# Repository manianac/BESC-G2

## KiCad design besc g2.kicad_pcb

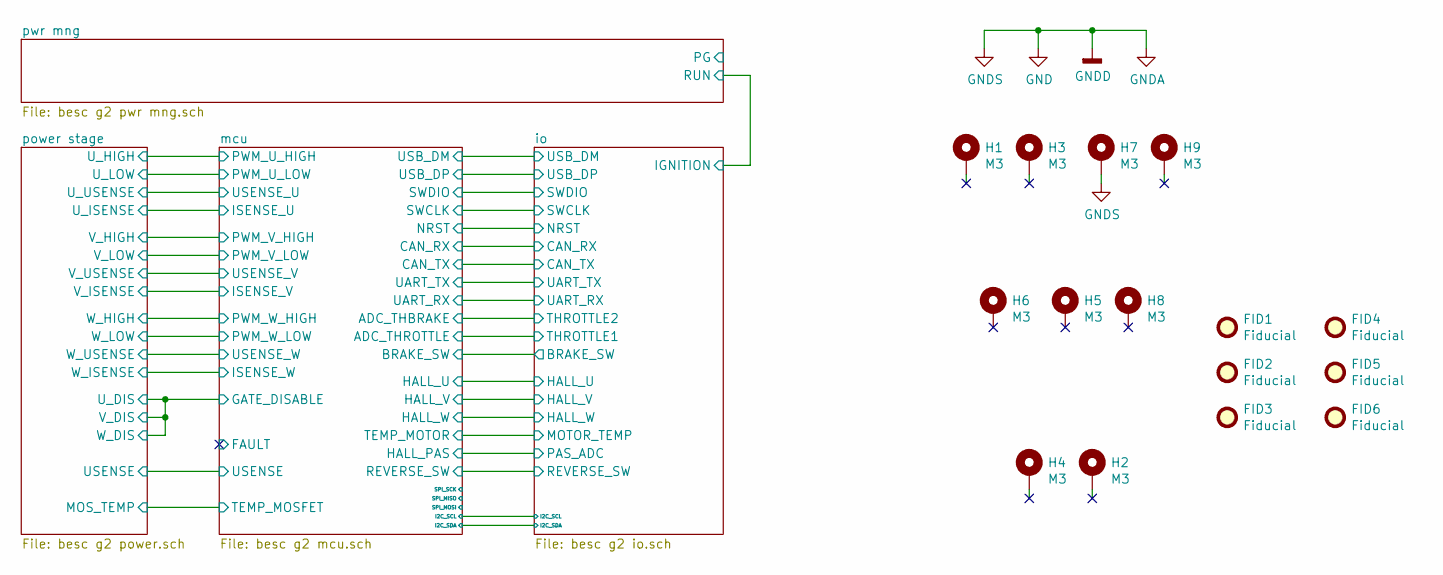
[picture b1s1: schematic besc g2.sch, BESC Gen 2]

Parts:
FID1, FID2, FID3, FID4, FID5, FID6: Fiducial; Fiducial_0.5mm_Mask1.5mm
H1, H2, H3, H4, H5, H6, H7, H8, H9: M3; MountingHole_3.2mm_M3_Pad_Via

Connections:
GND: H7.1; also elsewhere on the board

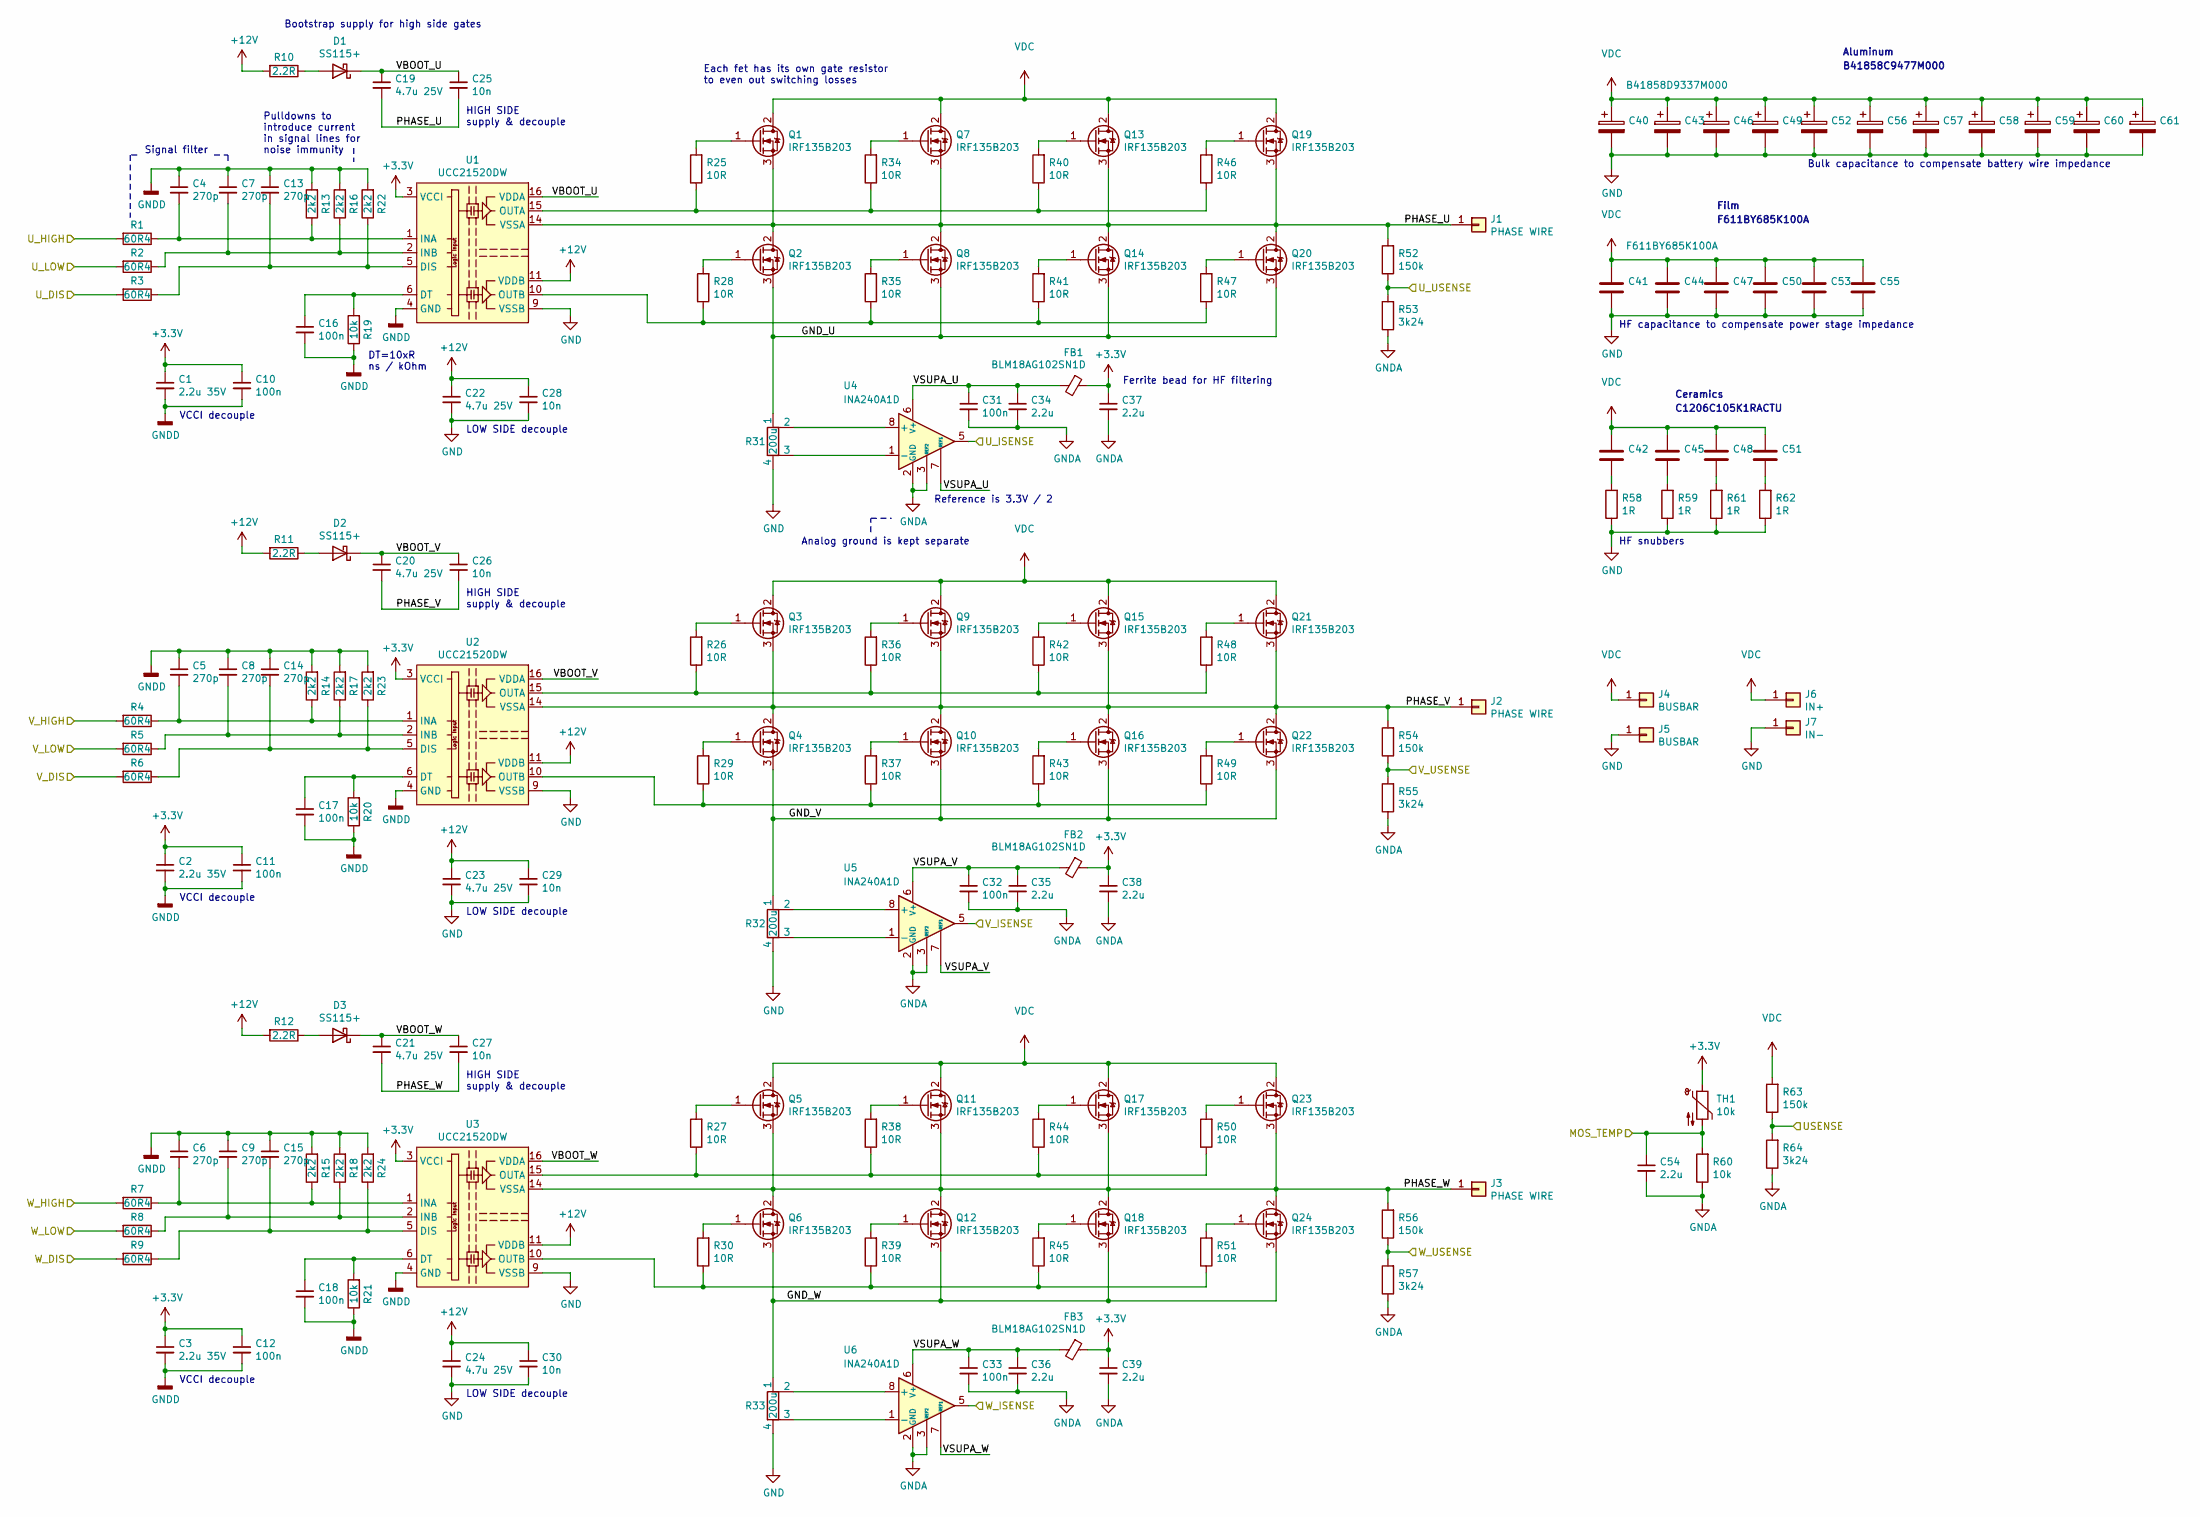
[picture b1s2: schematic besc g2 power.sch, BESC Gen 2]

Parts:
C1, C2, C3: 2.2u 35V; C_0805_2012Metric
C4, C5, C6, C7, C8, C9, C13, C14, C15: 270p; C_0603_1608Metric
C10, C11, C12, C16, C17, C18, C31, C32, C33: 100n; C_0603_1608Metric
C19, C20, C21, C22, C23, C24: 4.7u 25V; C_1206_3216Metric
C25, C26, C27, C28, C29, C30: 10n; C_0603_1608Metric
C34, C35, C36, C37, C38, C39, C54: 2.2u; C_0603_1608Metric
C40, C43, C46, C49, C52, C56, C57, C58, C59, C60, C61: B41858D9337M000; C_Radial_D18.0mm_H25mm_P7.50mm
C41, C44, C47, C50, C53, C55: F611BY685K100A; C_Rect_L18.0mm_W11.0mm_P15.00mm_FKS3_FKP3
C42, C45, C48, C51: C1206C105K1RACTU; C_1206_3216Metric
D1, D2, D3: SS115+; D_SMA
FB1, FB2, FB3: BLM18AG102SN1D; L_0603_1608Metric
J1, J2, J3: PHASE WIRE; 8awg_wirepad
J4, J5: BUSBAR; busbar1
J6: IN+; 8awg_wirepad
J7: IN-; 8awg_wirepad
Q1, Q2, Q3, Q4, Q5, Q6, Q7, Q8, Q9, Q10, Q11, Q12, Q13, Q14, Q15, Q16, Q17, Q18, Q19, Q20, Q21, Q22, Q23, Q24: IRF135B203; TO-220-3_hor_tabup
R1, R2, R3, R4, R5, R6, R7, R8, R9: 60R4; R_0603_1608Metric
R10, R11, R12: 2.2R; R_1206_3216Metric
R13, R14, R15, R16, R17, R18, R22, R23, R24: 2k2; R_0603_1608Metric
R19, R20, R21, R60: 10k; R_0603_1608Metric
R25, R26, R27, R28, R29, R30, R34, R35, R36, R37, R38, R39, R40, R41, R42, R43, R44, R45, R46, R47, R48, R49, R50, R51: 10R; R_0805_2012Metric
R31, R32, R33: 200u; LRMAP5930x
R52, R54, R56, R63: 150k; R_0805_2012Metric
R53, R55, R57, R64: 3k24; R_0603_1608Metric
R58, R59, R61, R62: 1R; R_1206_3216Metric
TH1: 10k; R_0603_1608Metric
U1, U2, U3: UCC21520DW; SOIC-16W_7.5x10.3mm_P1.27mm
U4, U5, U6: INA240A1D; SOIC-8_3.9x4.9mm_P1.27mm

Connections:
+3V3: C1.1, C2.1, C3.1, C10.1, C11.1, C12.1, C37.1, C38.1, C39.1, FB1.1, FB2.1, FB3.1, TH1.1, U1.3 (VCCI), U1.8 (VCCI), U2.3 (VCCI), U2.8 (VCCI), U3.3 (VCCI), U3.8 (VCCI); also elsewhere on the board
+12V: C22.1, C23.1, C24.1, C28.1, C29.1, C30.1, R10.2, R11.2, R12.2, U1.11 (VDDB), U2.11 (VDDB), U3.11 (VDDB); also elsewhere on the board
/mcu/GATE_DISABLE: R3.2, R6.2, R9.2; also elsewhere on the board
/mcu/ISENSE_U: U4.5; also elsewhere on the board
/mcu/ISENSE_V: U5.5; also elsewhere on the board
/mcu/ISENSE_W: U6.5; also elsewhere on the board
/mcu/PWM_U_HIGH: R1.2; also elsewhere on the board
/mcu/PWM_U_LOW: R2.2; also elsewhere on the board
/mcu/PWM_V_HIGH: R4.2; also elsewhere on the board
/mcu/PWM_V_LOW: R5.2; also elsewhere on the board
/mcu/PWM_W_HIGH: R7.2; also elsewhere on the board
/mcu/PWM_W_LOW: R8.2; also elsewhere on the board
/mcu/USENSE: R63.1, R64.2; also elsewhere on the board
/mcu/USENSE_U: R52.1, R53.2; also elsewhere on the board
/mcu/USENSE_V: R54.1, R55.2; also elsewhere on the board
/mcu/USENSE_W: R56.1, R57.2; also elsewhere on the board
/power stage/GND_U: Q2.3 (S), Q8.3 (S), Q14.3 (S), Q20.3 (S), R31.1
/power stage/GND_V: Q4.3 (S), Q10.3 (S), Q16.3 (S), Q22.3 (S), R32.1
/power stage/GND_W: Q6.3 (S), Q12.3 (S), Q18.3 (S), Q24.3 (S), R33.1
/power stage/MOS_TEMP: C54.1, R60.2, TH1.2; also elsewhere on the board
/power stage/PHASE_U: C19.2, C25.2, J1.1, Q1.3 (S), Q2.2 (D), Q7.3 (S), Q8.2 (D), Q13.3 (S), Q14.2 (D), Q19.3 (S), Q20.2 (D), R52.2, U1.14 (VSSA)
/power stage/PHASE_V: C20.2, C26.2, J2.1, Q3.3 (S), Q4.2 (D), Q9.3 (S), Q10.2 (D), Q15.3 (S), Q16.2 (D), Q21.3 (S), Q22.2 (D), R54.2, U2.14 (VSSA)
/power stage/PHASE_W: C21.2, C27.2, J3.1, Q5.3 (S), Q6.2 (D), Q11.3 (S), Q12.2 (D), Q17.3 (S), Q18.2 (D), Q23.3 (S), Q24.2 (D), R56.2, U3.14 (VSSA)
/power stage/VBOOT_U: C19.1, C25.1, D1.1 (K), U1.16 (VDDA)
/power stage/VBOOT_V: C20.1, C26.1, D2.1 (K), U2.16 (VDDA)
/power stage/VBOOT_W: C21.1, C27.1, D3.1 (K), U3.16 (VDDA)
/power stage/VSUPA_U: C31.1, C34.1, FB1.2, U4.6 (V+), U4.7 (REF1)
/power stage/VSUPA_V: C32.1, C35.1, FB2.2, U5.6 (V+), U5.7 (REF1)
/power stage/VSUPA_W: C33.1, C36.1, FB3.2, U6.6 (V+), U6.7 (REF1)
GND: C1.2, C2.2, C3.2, C4.1, C5.1, C6.1, C7.1, C8.1, C9.1, C10.2, C11.2, C12.2, C13.1, C14.1, C15.1, C16.2, C17.2, C18.2, C22.2, C23.2, C24.2, C28.2, C29.2, C30.2, C31.2, C32.2, C33.2, C34.2, C35.2, C36.2, C37.2, C38.2, C39.2, C40.2, C41.2, C43.2, C44.2, C46.2, C47.2, C49.2, C50.2, C52.2, C53.2, C54.2, C55.2, C56.2, C57.2, C58.2, C59.2, C60.2, C61.2, J5.1, J7.1, R13.2, R14.2, R15.2, R16.2, R17.2, R18.2, R19.1, R20.1, R21.1, R22.2, R23.2, R24.2, R31.4, R32.4, R33.4, R53.1, R55.1, R57.1, R58.1, R59.1, R60.1, R61.1, R62.1, R64.1, U1.4 (GND), U1.9 (VSSB), U2.4 (GND), U2.9 (VSSB), U3.4 (GND), U3.9 (VSSB), U4.2 (GND), U4.3 (REF2), U4.4 (GND), U5.2 (GND), U5.3 (REF2), U5.4 (GND), U6.2 (GND), U6.3 (REF2), U6.4 (GND); also elsewhere on the board
unnamed: C4.2, R1.1, R13.1, U1.1 (INA)
unnamed: C5.2, R4.1, R14.1, U2.1 (INA)
unnamed: C6.2, R7.1, R15.1, U3.1 (INA)
unnamed: C7.2, R2.1, R16.1, U1.2 (INB)
unnamed: C8.2, R5.1, R17.1, U2.2 (INB)
unnamed: C9.2, R8.1, R18.1, U3.2 (INB)
unnamed: C13.2, R3.1, R22.1, U1.5 (DIS)
unnamed: C14.2, R6.1, R23.1, U2.5 (DIS)
unnamed: C15.2, R9.1, R24.1, U3.5 (DIS)
unnamed: C16.1, R19.2, U1.6 (DT)
unnamed: C17.1, R20.2, U2.6 (DT)
unnamed: C18.1, R21.2, U3.6 (DT)
unnamed: C42.2, R58.2
unnamed: C45.2, R59.2
unnamed: C48.2, R61.2
unnamed: C51.2, R62.2
unnamed: D1.2 (A), R10.1
unnamed: D2.2 (A), R11.1
unnamed: D3.2 (A), R12.1
unnamed: Q1.1 (G), R25.2
unnamed: Q2.1 (G), R28.2
unnamed: Q3.1 (G), R26.2
unnamed: Q4.1 (G), R29.2
unnamed: Q5.1 (G), R27.2
unnamed: Q6.1 (G), R30.2
unnamed: Q7.1 (G), R34.2
unnamed: Q8.1 (G), R35.2
unnamed: Q9.1 (G), R36.2
unnamed: Q10.1 (G), R37.2
unnamed: Q11.1 (G), R38.2
unnamed: Q12.1 (G), R39.2
unnamed: Q13.1 (G), R40.2
unnamed: Q14.1 (G), R41.2
unnamed: Q15.1 (G), R42.2
unnamed: Q16.1 (G), R43.2
unnamed: Q17.1 (G), R44.2
unnamed: Q18.1 (G), R45.2
unnamed: Q19.1 (G), R46.2
unnamed: Q20.1 (G), R47.2
unnamed: Q21.1 (G), R48.2
unnamed: Q22.1 (G), R49.2
unnamed: Q23.1 (G), R50.2
unnamed: Q24.1 (G), R51.2
unnamed: R25.1, R34.1, R40.1, R46.1, U1.15 (OUTA)
unnamed: R26.1, R36.1, R42.1, R48.1, U2.15 (OUTA)
unnamed: R27.1, R38.1, R44.1, R50.1, U3.15 (OUTA)
unnamed: R28.1, R35.1, R41.1, R47.1, U1.10 (OUTB)
unnamed: R29.1, R37.1, R43.1, R49.1, U2.10 (OUTB)
unnamed: R30.1, R39.1, R45.1, R51.1, U3.10 (OUTB)
unnamed: R31.2, U4.8 (+)
unnamed: R31.3, U4.1 (-)
unnamed: R32.2, U5.8 (+)
unnamed: R32.3, U5.1 (-)
unnamed: R33.2, U6.8 (+)
unnamed: R33.3, U6.1 (-)
VDC: C40.1, C41.1, C42.1, C43.1, C44.1, C45.1, C46.1, C47.1, C48.1, C49.1, C50.1, C51.1, C52.1, C53.1, C55.1, C56.1, C57.1, C58.1, C59.1, C60.1, C61.1, J4.1, J6.1, Q1.2 (D), Q3.2 (D), Q5.2 (D), Q7.2 (D), Q9.2 (D), Q11.2 (D), Q13.2 (D), Q15.2 (D), Q17.2 (D), Q19.2 (D), Q21.2 (D), Q23.2 (D), R63.2; also elsewhere on the board

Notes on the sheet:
LOW SIDE decouple
HIGH SIDE supply & decouple
Aluminum
Film
Ceramics
F611BY685K100A
B41858C9477M000
C1206C105K1RACTU
VCCI decouple
DT=10xR ns / kOhm
Reference is 3.3V / 2
Ferrite bead for HF filtering
Each fet has its own gate resistor to even out switching losses
Bulk capacitance to compensate battery wire impedance
HF capacitance to compensate power stage impedance
HF snubbers
Pulldowns to introduce current in signal lines for noise immunity
Bootstrap supply for high side gates
Signal filter
Analog ground is kept separate

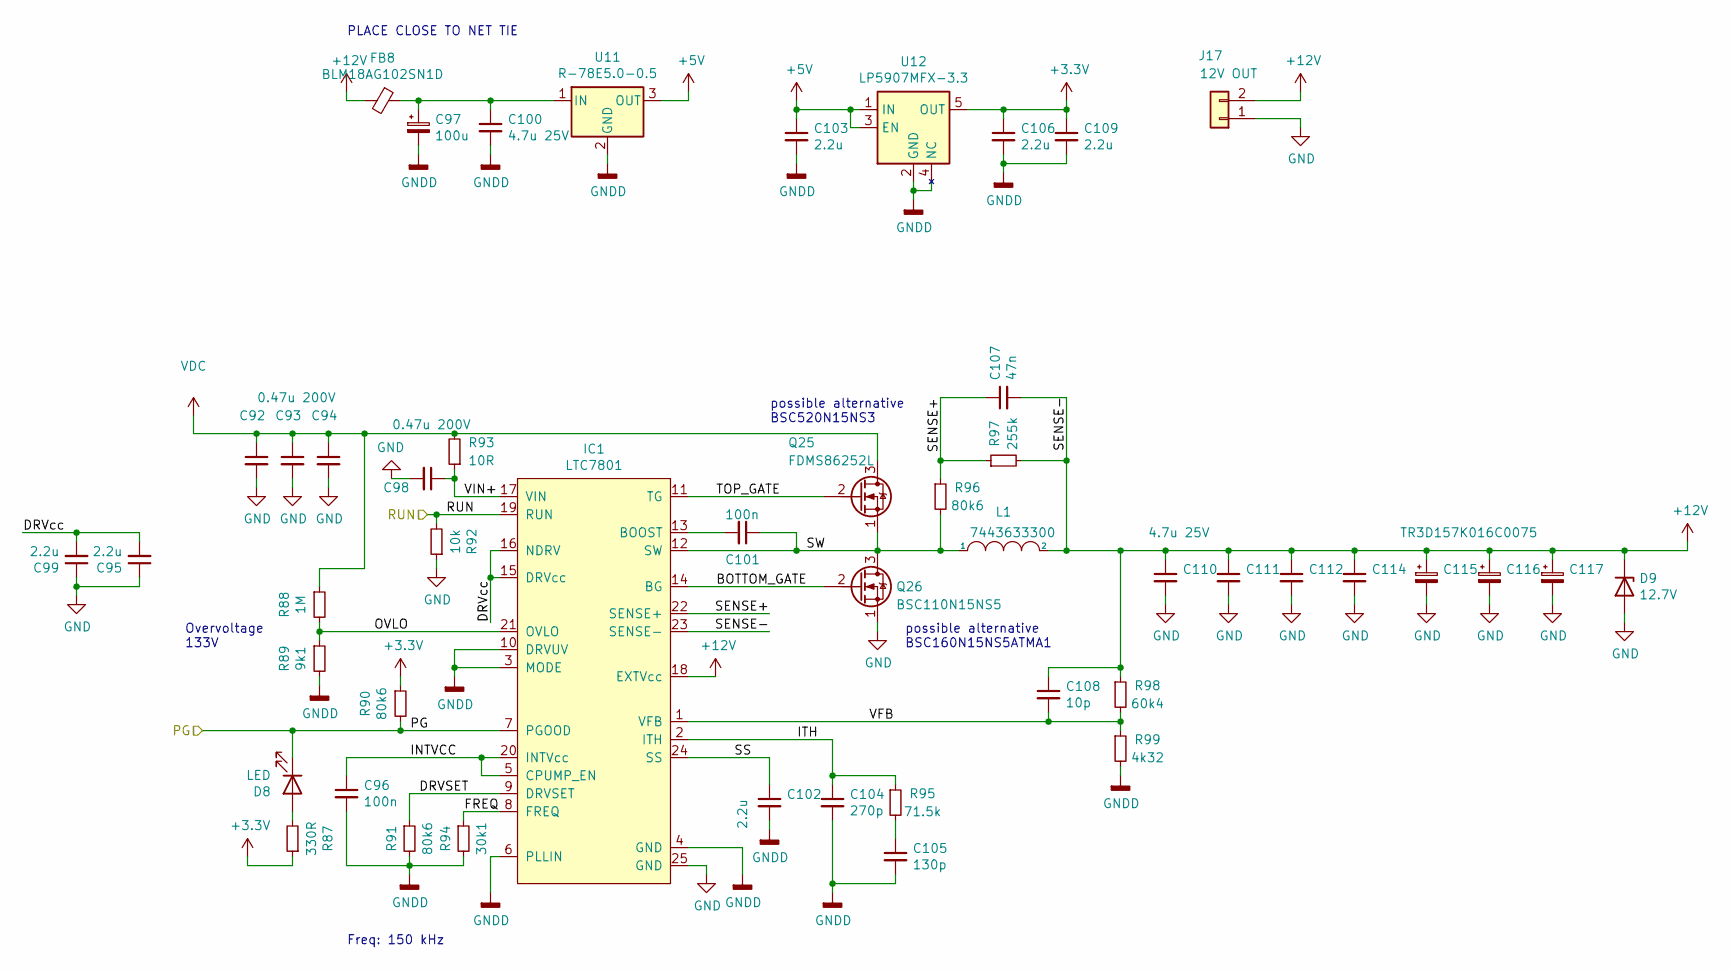
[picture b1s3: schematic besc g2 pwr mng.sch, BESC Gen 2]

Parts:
C92, C93, C94, C98: 0.47u 200V; C_1210_3225Metric
C95, C99, C102, C103, C106, C109: 2.2u; C_0603_1608Metric
C96, C101: 100n; C_0603_1608Metric
C97: 100u; CP_EIA-6032-28_Kemet-C; PART TAJD107M016RNJ
C100, C110, C111, C112, C114: 4.7u 25V; C_1206_3216Metric
C104: 270p; C_0603_1608Metric
C105: 130p; C_0603_1608Metric
C107: 47n; C_0603_1608Metric
C108: 10p; C_0603_1608Metric
C115, C116, C117: TR3D157K016C0075; CP_EIA-7343-31_Kemet-D
D8: LED; LED_0603_1608Metric
D9: 12.7V; D_SMA
FB8: BLM18AG102SN1D; L_0603_1608Metric
IC1: LTC7801; QFN-24-1EP_4x5mm_P0.5mm_EP2.65x3.65mm
J17: 12V OUT; AMASS_XT30U-M_1x02_P5.0mm_Vertical
L1: 7443633300; WE-HCF-2013
Q25: FDMS86252L; TDSON-8-MOS
Q26: BSC110N15NS5; TDSON-8-MOS
R87: 330R; R_0603_1608Metric
R88: 1M; R_0603_1608Metric
R89: 9k1; R_0603_1608Metric
R90, R91, R96: 80k6; R_0603_1608Metric
R92: 10k; R_0603_1608Metric
R93: 10R; R_0805_2012Metric
R94: 30k1; R_0603_1608Metric
R95: 71.5k; R_0603_1608Metric
R97: 255k; R_0603_1608Metric
R98: 60k4; R_0603_1608Metric
R99: 4k32; R_0603_1608Metric
U11: R-78E5.0-0.5; Converter_DCDC_RECOM_R-78E-0.5_THT
U12: LP5907MFX-3.3; SOT-23-5

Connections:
+3V3: C106.1, C109.1, R87.1, R90.1, U12.5 (OUT); also elsewhere on the board
+5V: C103.1, U11.3 (OUT), U12.1 (IN), U12.3 (EN); also elsewhere on the board
+12V: C107.2, C108.1, C110.1, C111.1, C112.1, C114.1, C115.1, C116.1, C117.1, D9.1 (K), FB8.2, IC1.18 (EXTVcc), IC1.23 (SENSE-), J17.2, L1.2, R97.2, R98.1; also elsewhere on the board
/io/IGNITION: IC1.19 (RUN), R92.2; also elsewhere on the board
/pwr mng/BOTTOM_GATE: IC1.14 (BG), Q26.2 (G)
/pwr mng/DRVSET: IC1.9 (DRVSET), R91.1
/pwr mng/DRVcc: C95.2, C99.2, IC1.15 (DRVcc), IC1.16 (NDRV)
/pwr mng/FREQ: IC1.8 (FREQ), R94.1
/pwr mng/INTVCC: C96.1, IC1.5 (CPUMP_EN), IC1.20 (INTVcc)
/pwr mng/ITH: C104.1, IC1.2 (ITH), R95.1
/pwr mng/OVLO: IC1.21 (OVLO), R88.2, R89.1
/pwr mng/PG: D8.1 (K), IC1.7 (PGOOD), R90.2
/pwr mng/SENSE+: C107.1, IC1.22 (SENSE+), R96.1, R97.1
/pwr mng/SS: C102.1, IC1.24 (SS)
/pwr mng/SW: C101.1, IC1.12 (SW), L1.1, Q25.1 (S), Q26.3 (D), R96.2
/pwr mng/TOP_GATE: IC1.11 (TG), Q25.2 (G)
/pwr mng/VFB: C108.2, IC1.1 (VFB), R98.2, R99.1
/pwr mng/VIN+: C98.1, IC1.17 (VIN), R93.1
GND: C92.2, C93.2, C94.2, C95.1, C96.2, C97.2, C98.2, C99.1, C100.2, C102.2, C103.2, C104.2, C105.2, C106.2, C109.2, C110.2, C111.2, C112.2, C114.2, C115.2, C116.2, C117.2, D9.2 (A), IC1.3 (MODE), IC1.4 (GND), IC1.6 (PLLIN), IC1.10 (DRVUV), IC1.25 (GND), J17.1, Q26.1 (S), R89.2, R91.2, R92.1, R94.2, R99.2, U11.2 (GND), U12.2 (GND), U12.4 (NC); also elsewhere on the board
unnamed: C97.1, C100.1, FB8.1, U11.1 (IN)
unnamed: C101.2, IC1.13 (BOOST)
unnamed: C105.1, R95.2
unnamed: D8.2 (A), R87.2
VDC: C92.1, C93.1, C94.1, Q25.3 (D), R88.1, R93.2; also elsewhere on the board

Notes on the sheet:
PLACE CLOSE TO NET TIE
Overvoltage 133V
Freq: 150 kHz
possible alternative BSC160N15NS5ATMA1
possible alternative BSC520N15NS3

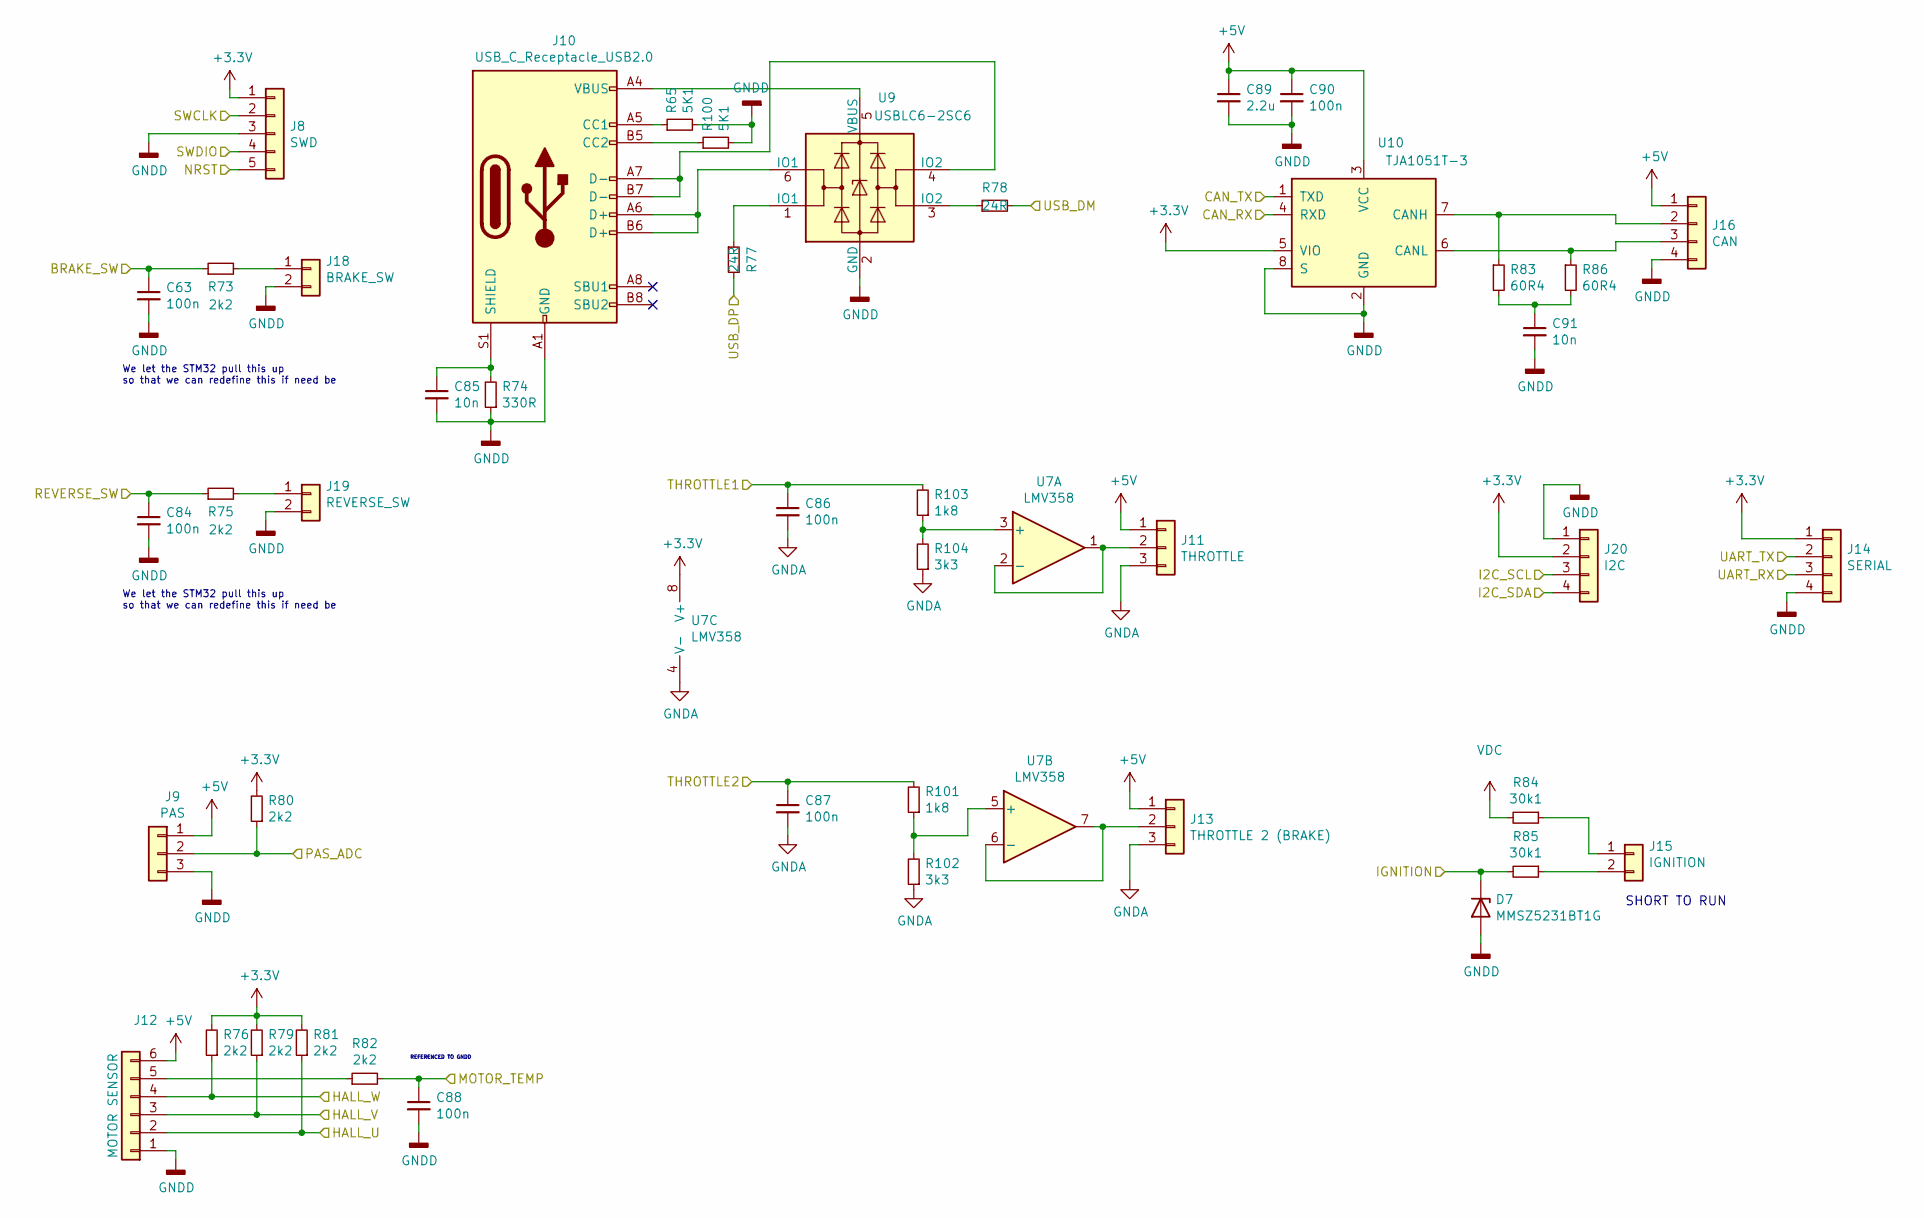
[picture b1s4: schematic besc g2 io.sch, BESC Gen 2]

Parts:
C63, C84, C86, C87, C88, C90: 100n; C_0603_1608Metric
C85, C91: 10n; C_0603_1608Metric
C89: 2.2u; C_0603_1608Metric
D7: MMSZ5231BT1G; D_SOD-123
J8: SWD; PinHeader_1x05_P2.54mm_Vertical
J9: PAS; PinHeader_1x03_P2.54mm_Vertical
J10: USB_C_Receptacle_USB2.0; GCT_USB4120-03-C_REVA
J11: THROTTLE; PinHeader_1x03_P2.54mm_Vertical
J12: MOTOR SENSOR; PinHeader_1x06_P2.54mm_Vertical
J13: THROTTLE 2 (BRAKE); PinHeader_1x03_P2.54mm_Vertical
J14: SERIAL; PinHeader_1x04_P2.54mm_Vertical
J15: IGNITION; PinHeader_1x02_P2.54mm_Vertical
J16: CAN; PinHeader_1x04_P2.54mm_Vertical
J18: BRAKE_SW; PinHeader_1x02_P2.54mm_Vertical
J19: REVERSE_SW; PinHeader_1x02_P2.54mm_Vertical
J20: I2C; PinSocket_1x04_P2.54mm_Vertical
R65, R100: 5K1; R_0603_1608Metric
R73, R75, R76, R79, R80, R81, R82: 2k2; R_0603_1608Metric
R74: 330R; R_0603_1608Metric
R77, R78: 24R; R_0603_1608Metric
R83, R86: 60R4; R_0603_1608Metric
R84, R85: 30k1; R_0603_1608Metric
R101, R103: 1k8; R_0603_1608Metric
R102, R104: 3k3; R_0603_1608Metric
U7: LMV358; SOIC-8_3.9x4.9mm_P1.27mm
U9: USBLC6-2SC6; SOT-666
U10: TJA1051T-3; SOIC-8_3.9x4.9mm_P1.27mm

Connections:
+3V3: J8.1, J14.1, J20.2, R76.2, R79.2, R80.2, R81.2, U7.8 (V+), U10.5 (VIO); also elsewhere on the board
+5V: C89.1, C90.1, J9.1, J11.1, J12.6, J13.1, J16.1, U10.3 (VCC); also elsewhere on the board
/io/BRAKE_SW: C63.1, R73.1; also elsewhere on the board
/io/CAN_RX: U10.4 (RXD); also elsewhere on the board
/io/CAN_TX: U10.1 (TXD); also elsewhere on the board
/io/HALL_U: J12.2, R81.1; also elsewhere on the board
/io/HALL_V: J12.3, R79.1; also elsewhere on the board
/io/HALL_W: J12.4, R76.1; also elsewhere on the board
/io/I2C_SCL: J20.3; also elsewhere on the board
/io/I2C_SDA: J20.4; also elsewhere on the board
/io/IGNITION: D7.1 (K), R85.2; also elsewhere on the board
/io/MOTOR_TEMP: C88.1, R82.2; also elsewhere on the board
/io/NRST: J8.5; also elsewhere on the board
/io/REVERSE_SW: C84.1, R75.1; also elsewhere on the board
/io/SWCLK: J8.2; also elsewhere on the board
/io/SWDIO: J8.4; also elsewhere on the board
/io/UART_RX: J14.3; also elsewhere on the board
/io/UART_TX: J14.2; also elsewhere on the board
/io/USB_DM: R78.2; also elsewhere on the board
/io/USB_DP: R77.2; also elsewhere on the board
/mcu/ADC_THBRAKE: C87.1, R101.2; also elsewhere on the board
/mcu/ADC_THROTTLE: C86.1, R103.2; also elsewhere on the board
/mcu/HALL_PAS: J9.2, R80.1; also elsewhere on the board
GND: C63.2, C84.2, C85.2, C86.2, C87.2, C88.2, C89.2, C90.2, C91.2, D7.2 (A), J8.3, J9.3, J10.A1 (GND), J10.A12 (GND), J10.B1 (GND), J10.B12 (GND), J11.3, J12.1, J13.3, J14.4, J16.4, J18.2, J19.2, J20.1, R65.2, R74.1, R100.2, R102.1, R104.1, U7.4 (V-), U9.2 (GND), U10.2 (GND), U10.8 (S); also elsewhere on the board
unnamed: C85.1, J10.S1 (SHIELD), R74.2
unnamed: C91.1, R83.2, R86.2
unnamed: J10.A4 (VBUS), J10.A9 (VBUS), J10.B4 (VBUS), J10.B9 (VBUS), U9.5 (VBUS)
unnamed: J10.A5 (CC1), R65.1
unnamed: J10.A6 (D+), J10.B6 (D+), U9.6 (IO1)
unnamed: J10.A7 (D-), J10.B7 (D-), U9.4 (IO2)
unnamed: J10.B5 (CC2), R100.1
unnamed: J11.2, U7.1, U7.2 (-)
unnamed: J12.5, R82.1
unnamed: J13.2, U7.6 (-), U7.7
unnamed: J15.1, R84.1
unnamed: J15.2, R85.1
unnamed: J16.2, R83.1, U10.7 (CANH)
unnamed: J16.3, R86.1, U10.6 (CANL)
unnamed: J18.1, R73.2
unnamed: J19.1, R75.2
unnamed: R77.1, U9.1 (IO1)
unnamed: R78.1, U9.3 (IO2)
unnamed: R101.1, R102.2, U7.5 (+)
unnamed: R103.1, R104.2, U7.3 (+)
VDC: R84.2; also elsewhere on the board

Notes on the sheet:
REFERENCED TO GNDD
SHORT TO RUN
We let the STM32 pull this up so that we can redefine this if need be

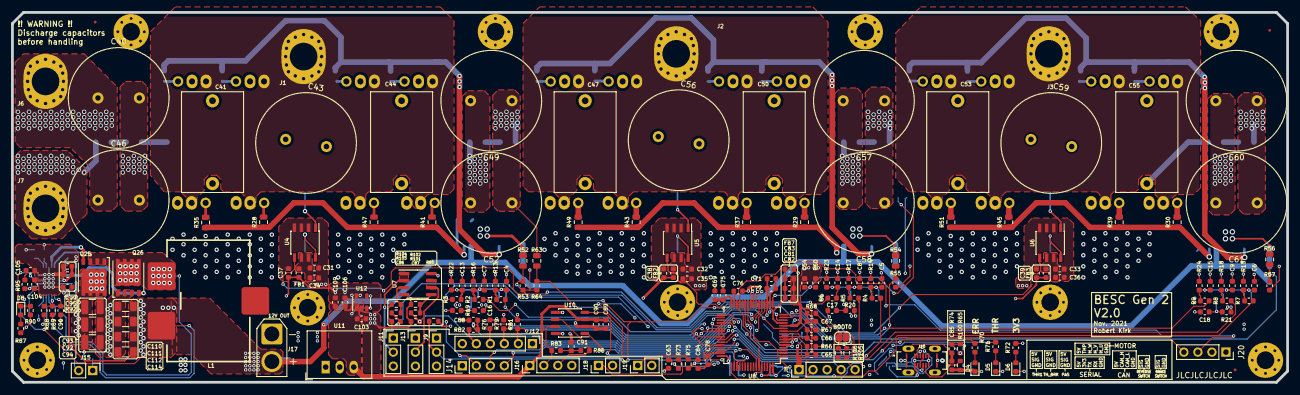
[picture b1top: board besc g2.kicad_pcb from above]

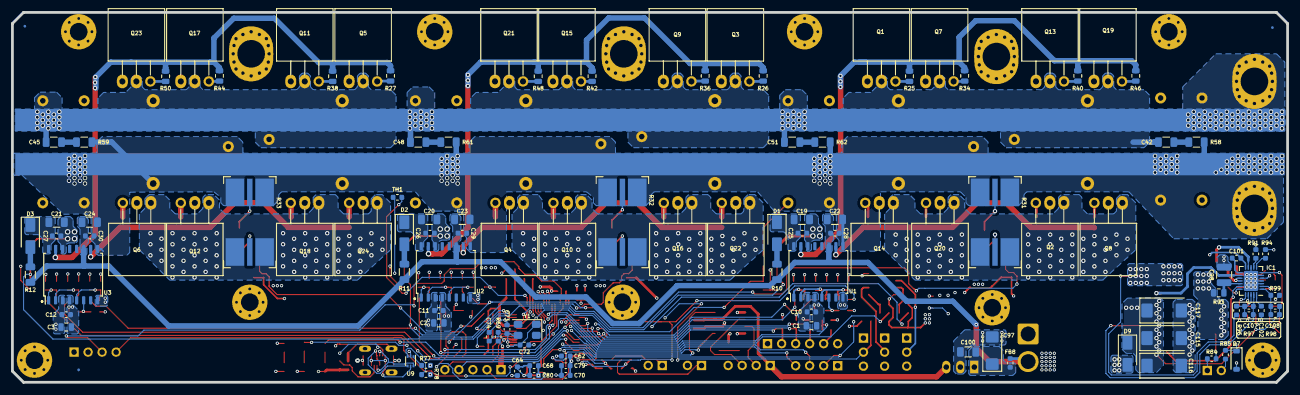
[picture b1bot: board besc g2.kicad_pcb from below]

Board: 4 copper layers, 231.0 x 67.0 mm, 314 parts (117 on the bottom side), 161 nets.

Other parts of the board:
C62, C64, C76, C78, C83: 2.2u; C_0603_1608Metric
C65, C66, C67: 270p; C_0603_1608Metric
C68, C69, C70, C71, C74, C82: 100n; C_0603_1608Metric
C72, C73: 15p; C_0603_1608Metric
C75, C77, C79, C80, C81: 10n; C_0603_1608Metric
D4: RED; LED_0603_1608Metric
D5: GREEN; LED_0603_1608Metric
D6: BLUE; LED_0603_1608Metric
FB7: BLM18AG102SN1D; L_0603_1608Metric
JP2: BOOT0; SolderJumper-2_P1.3mm_Open_RoundedPad1.0x1.5mm
R66, R67, R68, R69, R70, R71, R72, R105: 2k2; R_0603_1608Metric
R106: 10k; R_0603_1608Metric
U8: STM32F405RGTx; LQFP-64_10x10mm_P0.5mm
Y1: MCSJK-7I-8.00-18-10-60-B-10; Crystal_SMD_5032-4Pin_5.0x3.2mm

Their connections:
+3V3: C62.1, C64.1, C68.1, C69.1, C70.1, C71.1, C75.1, C77.1, C79.1, C80.1, FB7.1, JP2.1, R69.1, R72.2, U8.1, U8.19, U8.32, U8.48, U8.64; also elsewhere on the board
/io/BRAKE_SW: U8.25; also elsewhere on the board
/io/CAN_RX: U8.33; also elsewhere on the board
/io/CAN_TX: U8.34; also elsewhere on the board
/io/HALL_U: U8.37; also elsewhere on the board
/io/HALL_V: U8.38; also elsewhere on the board
/io/HALL_W: U8.39; also elsewhere on the board
/io/I2C_SCL: U8.29; also elsewhere on the board
/io/I2C_SDA: U8.30; also elsewhere on the board
/io/MOTOR_TEMP: U8.20; also elsewhere on the board
/io/NRST: C74.1, R69.2, U8.7; also elsewhere on the board
/io/REVERSE_SW: U8.51; also elsewhere on the board
/io/SWCLK: U8.49; also elsewhere on the board
/io/SWDIO: U8.46; also elsewhere on the board
/io/UART_RX: U8.59; also elsewhere on the board
/io/UART_TX: U8.58; also elsewhere on the board
/io/USB_DM: U8.44; also elsewhere on the board
/io/USB_DP: U8.45; also elsewhere on the board
/mcu/ADC_THBRAKE: U8.22; also elsewhere on the board
/mcu/ADC_THROTTLE: U8.21; also elsewhere on the board
/mcu/BOOT0: JP2.2, R105.1, R106.1
/mcu/GATE_DISABLE: U8.50; also elsewhere on the board
/mcu/HALL_PAS: U8.24; also elsewhere on the board
/mcu/ISENSE_U: R66.2; also elsewhere on the board
/mcu/ISENSE_U_FILT: C65.2, R66.1, U8.8
/mcu/ISENSE_V: R67.2; also elsewhere on the board
/mcu/ISENSE_V_FILT: C66.2, R67.1, U8.9
/mcu/ISENSE_W: R68.2; also elsewhere on the board
/mcu/ISENSE_W_FILT: C67.2, R68.1, U8.10
/mcu/PWM_U_HIGH: U8.41; also elsewhere on the board
/mcu/PWM_U_LOW: U8.23; also elsewhere on the board
/mcu/PWM_V_HIGH: U8.42; also elsewhere on the board
/mcu/PWM_V_LOW: U8.26; also elsewhere on the board
/mcu/PWM_W_HIGH: U8.43; also elsewhere on the board
/mcu/PWM_W_LOW: U8.27; also elsewhere on the board
/mcu/USENSE: U8.11; also elsewhere on the board
/mcu/USENSE_U: U8.14; also elsewhere on the board
/mcu/USENSE_V: U8.15; also elsewhere on the board
/mcu/USENSE_W: U8.16; also elsewhere on the board
/power stage/MOS_TEMP: U8.17; also elsewhere on the board
GND: C62.2, C64.2, C65.1, C66.1, C67.1, C68.2, C69.2, C70.2, C71.2, C72.2, C73.2, C74.2, C75.2, C76.2, C77.2, C78.2, C79.2, C80.2, C81.2, C82.2, C83.2, D4.1, D5.1, D6.1, R105.2, U8.12, U8.18, U8.63; also elsewhere on the board
unnamed: C72.1, U8.5, Y1.1
unnamed: C73.1, U8.6, Y1.2
unnamed: C76.1, U8.31
unnamed: C78.1, U8.47
unnamed: C81.1, C82.1, C83.1, FB7.2, U8.13
unnamed: D4.2, R70.1
unnamed: D5.2, R71.1
unnamed: D6.2, R72.1
unnamed: R70.2, U8.36
unnamed: R71.2, U8.35
unnamed: R106.2, U8.60

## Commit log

2021-11-07 Added brakes, i2c
2021-11-26 Test commit
2021-11-26 Deleted test file
